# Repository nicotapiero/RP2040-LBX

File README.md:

# RP2040 LBX Compatible PCB

Initially forked from the [4.0 Version of the GRAM-SLIM](https://github.com/GRAMCTRL/GRAM-SLIM)

Thanks @beyondperfectly in the JFA Discord for the intial measurements: https://discord.com/channels/659775676542353438/888150700322861076/1038660816783802388

### Required Footprint Libraries:

* https://github.com/quark-works/qw-footprints/ (added as Git Submodule)
* [SW_choc_v1_HS_1u](https://github.com/ebastler/marbastlib/blob/6b0a9a73f579e377816d60b58eac2b3252de7868/footprints/marbastlib-choc.pretty/SW_choc_v1_HS_CPG135001S30_1u.kicad_mod)
* [SOIC-8_5.23x5.23mm_P1.27mm](https://github.com/KiCad/kicad-footprints/blob/master/Package_SO.pretty/SOIC-8_5.23x5.23mm_P1.27mm.kicad_mod)
* [CON_TC2030_outlined](https://github.com/ebastler/marbastlib/blob/6b0a9a73f579e377816d60b58eac2b3252de7868/footprints/marbastlib-various.pretty/CON_TC2030_outlined.kicad_mod)
* [ul_TS-1187A-B-A-B](https://app.ultralibrarian.com/details/34b5192a-fcd3-11ec-b159-0a34d6323d74/XKB-Connectivity/TS-1187A-B-A-B?open=backlink)

`.gitignore` for KiCad from [official Github repo](https://github.com/github/gitignore/blob/5b24c9042da72fcdcbe77dd5043243c987151d64/KiCad.gitignore)

Button layout to-scale diagram provided by LBX in their manual: https://docs.google.com/document/d/1tbTJEMjoW81OzD7IcGiDwz86cqZ35NQjBmwLq3tH4vI/edit?tab=t.0

Buttons confirmed rotated 9 degrees: https://discord.com/channels/659775676542353438/888150700322861076/1085662648756097205

PS Buttons confirmed TS-1187A-C-G-A or TS-1187A-C-G-B: https://discord.com/channels/659775676542353438/888150700322861076/1376599778439463015

## Disclaimer

This is an independent, community-developed replacement PCB compatible with the JFA LBX controller.

This project is not affiliated with, endorsed by, or sponsored by JFA. "JFA" and "LBX" are used solely to describe compatibility.

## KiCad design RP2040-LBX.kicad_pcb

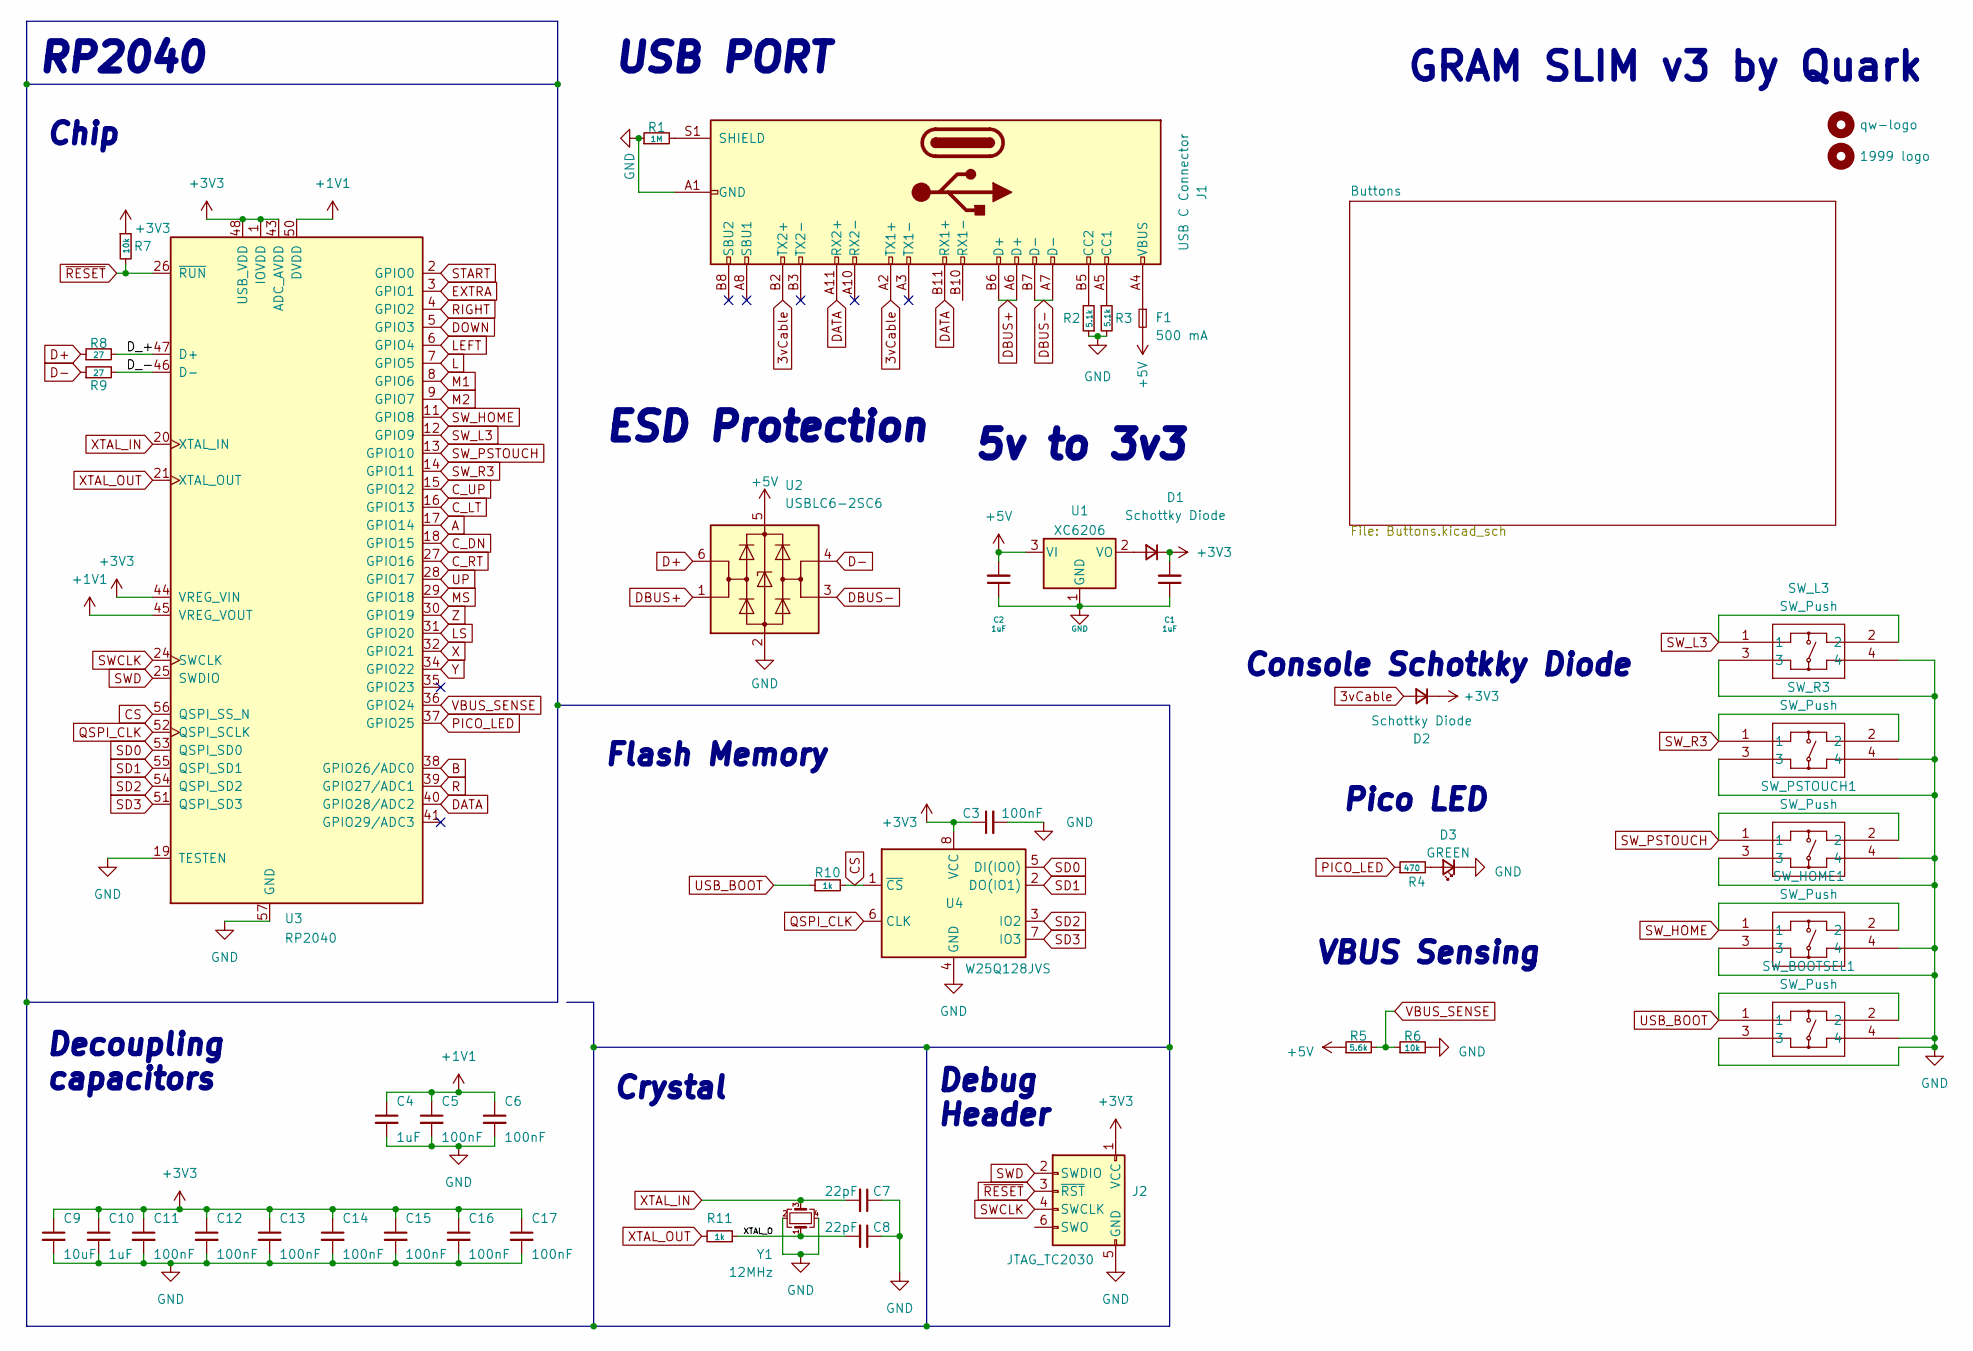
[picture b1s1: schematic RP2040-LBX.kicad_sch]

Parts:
C1, C2, C4, C10: 1uF; C_0402_1005Metric; LCSC C52923
C3, C5, C6, C11, C12, C13, C14, C15, C16, C17: 100nF; C_0402_1005Metric; LCSC C1525
C7, C8: 22pF; C_0402_1005Metric; LCSC C1555
C9: 10uF; C_0402_1005Metric; LCSC C15525
D1, D2: Schottky Diode; D_SOD-123; LCSC C130880
D3: GREEN; LED_0805_2012Metric; LCSC C2297
F1: 500 mA; Fuse_1206_3216Metric; LCSC C2836286
H1: qw-logo; qw new logo silk + copper md
H2: 1999 logo; 1999 logo md
J1: USB C Connector; TYPE-C_24P_QCHT; LCSC C456013
J2: JTAG_TC2030; CON_TC2030_outlined
R1: 1M; R_0603_1608Metric; LCSC C22935
R2, R3: 5.1k; R_0402_1005Metric; LCSC C25905
R4: 470; R_0402_1005Metric; LCSC C25117
R5: 5.6k; R_0603_1608Metric; LCSC C23189
R6: 10k; R_0603_1608Metric; LCSC C25804
R7: 10k; R_0402_1005Metric; LCSC C25744
R8, R9: 27; R_0603_1608Metric; LCSC C25190
R10, R11: 1k; R_0402_1005Metric; LCSC C11702
SW_BOOTSEL1: SW_Push; TS-1187A-B-A-B_XKB; LCSC C318886
SW_HOME1: SW_Push; TS-1187A-B-A-B_XKB; LCSC C318886
SW_L3: SW_Push; TS-1187A-B-A-B_XKB; LCSC C318886
SW_PSTOUCH1: SW_Push; TS-1187A-B-A-B_XKB; LCSC C318886
SW_R3: SW_Push; TS-1187A-B-A-B_XKB; LCSC C318886
U1: XC6206; SOT-23; LCSC C5446
U2: USBLC6-2SC6; SOT-23-6; LCSC C2827654
U3: RP2040; RP2040-QFN-56; LCSC C2040
U4: W25Q128JVS; SOIC-8_5.23x5.23mm_P1.27mm; LCSC C97521
Y1: 12MHz; Crystal_SMD_3225-4Pin_3.2x2.5mm; LCSC C9002

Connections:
3vCable: D2.2 (A), J1.A2 (TX1+), J1.B2 (TX2+)
+1V1: C4.1, C5.1, C6.1, U3.23 (DVDD), U3.45 (VREG_VOUT), U3.50 (DVDD)
+3V3: C1.2, C3.1, C9.1, C10.1, C11.1, C12.1, C13.1, C14.1, C15.1, C16.1, C17.1, D1.1 (K), D2.1 (K), J2.1 (VCC), R7.1, U3.1 (IOVDD), U3.10 (IOVDD), U3.22 (IOVDD), U3.33 (IOVDD), U3.42 (IOVDD), U3.43 (ADC_AVDD), U3.44 (VREG_VIN), U3.48 (USB_VDD), U3.49 (IOVDD), U4.8 (VCC)
+5V: C2.2, F1.2, R5.1, U1.3 (VI), U2.5 (VBUS)
/D_+: R8.2, U3.47 (D+)
/D_-: R9.2, U3.46 (D-)
/XTAL_O: C8.2, R11.1, Y1.1
A: U3.17 (GPIO14); also elsewhere on the board
B: U3.38 (GPIO26/ADC0); also elsewhere on the board
CS: R10.2, U3.56 (QSPI_SS_N), U4.1 (~CS)
C_DN: U3.18 (GPIO15); also elsewhere on the board
C_LT: U3.16 (GPIO13); also elsewhere on the board
C_RT: U3.27 (GPIO16); also elsewhere on the board
C_UP: U3.15 (GPIO12); also elsewhere on the board
D+: R8.1, U2.6 (I/O1)
D-: R9.1, U2.4 (I/O2)
DATA: J1.A11 (RX2+), J1.B11 (RX1+), U3.40 (GPIO28/ADC2)
DBUS+: J1.A6 (D+), J1.B6 (D+), U2.1 (I/O1)
DBUS-: J1.A7 (D-), J1.B7 (D-), U2.3 (I/O2)
DOWN: U3.5 (GPIO3); also elsewhere on the board
EXTRA: U3.3 (GPIO1); also elsewhere on the board
GND: C1.1, C2.1, C3.2, C4.2, C5.2, C6.2, C7.1, C8.1, C9.2, C10.2, C11.2, C12.2, C13.2, C14.2, C15.2, C16.2, C17.2, D3.1 (K), J1.A1 (GND), J1.A12 (GND), J1.B1 (GND), J1.B12 (GND), J2.5 (GND), R1.1, R2.1, R3.2, R6.2, SW_BOOTSEL1.3, SW_BOOTSEL1.4, SW_HOME1.3, SW_HOME1.4, SW_L3.3, SW_L3.4, SW_PSTOUCH1.3, SW_PSTOUCH1.4, SW_R3.3, SW_R3.4, U1.1 (GND), U2.2 (GND), U3.19 (TESTEN), U3.57 (GND), U4.4 (GND), Y1.2, Y1.4; also elsewhere on the board
L: U3.7 (GPIO5); also elsewhere on the board
LEFT: U3.6 (GPIO4); also elsewhere on the board
LS: U3.31 (GPIO20); also elsewhere on the board
M1: U3.8 (GPIO6); also elsewhere on the board
M2: U3.9 (GPIO7); also elsewhere on the board
MS: U3.29 (GPIO18); also elsewhere on the board
unnamed: D1.2 (A), U1.2 (VO)
unnamed: D3.2 (A), R4.2
unnamed: F1.1, J1.A4 (VBUS), J1.A9 (VBUS), J1.B4 (VBUS), J1.B9 (VBUS)
unnamed: J1.A5 (CC1), R3.1
unnamed: J1.B5 (CC2), R2.2
unnamed: J1.S1 (SHIELD), R1.2
PICO_LED: R4.1, U3.37 (GPIO25)
QSPI_CLK: U3.52 (QSPI_SCLK), U4.6 (CLK)
R: U3.39 (GPIO27/ADC1); also elsewhere on the board
RIGHT: U3.4 (GPIO2); also elsewhere on the board
SD0: U3.53 (QSPI_SD0), U4.5 (DI(IO0))
SD1: U3.55 (QSPI_SD1), U4.2 (DO(IO1))
SD2: U3.54 (QSPI_SD2), U4.3 (IO2)
SD3: U3.51 (QSPI_SD3), U4.7 (IO3)
START: U3.2 (GPIO0); also elsewhere on the board
SWCLK: J2.4 (SWCLK), U3.24 (SWCLK)
SWD: J2.2 (SWDIO), U3.25 (SWDIO)
SW_HOME: SW_HOME1.1, SW_HOME1.2, U3.11 (GPIO8)
SW_L3: SW_L3.1, SW_L3.2, U3.12 (GPIO9)
SW_PSTOUCH: SW_PSTOUCH1.1, SW_PSTOUCH1.2, U3.13 (GPIO10)
SW_R3: SW_R3.1, SW_R3.2, U3.14 (GPIO11)
UP: U3.28 (GPIO17); also elsewhere on the board
USB_BOOT: R10.1, SW_BOOTSEL1.1, SW_BOOTSEL1.2
VBUS_SENSE: R5.2, R6.1, U3.36 (GPIO24)
X: U3.32 (GPIO21); also elsewhere on the board
XTAL_IN: C7.2, U3.20 (XTAL_IN), Y1.3
XTAL_OUT: R11.2, U3.21 (XTAL_OUT)
Y: U3.34 (GPIO22); also elsewhere on the board
Z: U3.30 (GPIO19); also elsewhere on the board
~RESET: J2.3 (~RST), R7.2, U3.26 (~RUN)

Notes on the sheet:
GRAM SLIM v3 by Quark
Flash Memory
5v to 3v3
Pico LED
Crystal
Chip
Console Schotkky Diode
RP2040
VBUS Sensing
Debug Header
USB PORT
ESD Protection
Decoupling capacitors

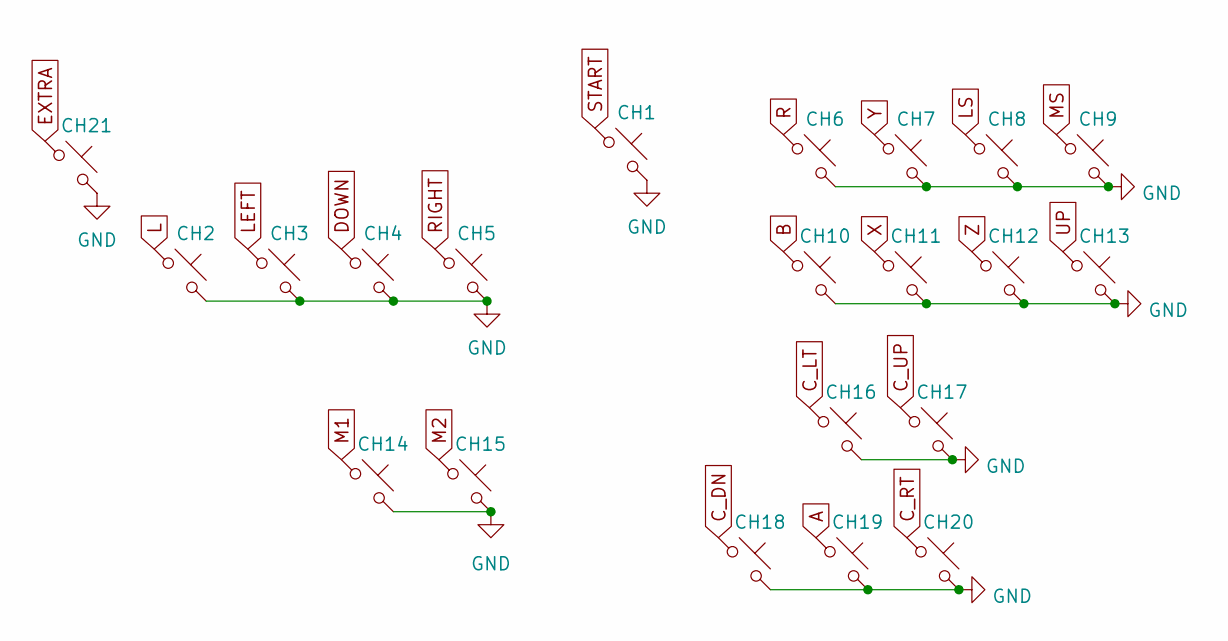
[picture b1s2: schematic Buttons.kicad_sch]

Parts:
CH1, CH2, CH3, CH4, CH5, CH6, CH7, CH8, CH9, CH10, CH11, CH12, CH13, CH14, CH15, CH16, CH17, CH18, CH19, CH20, CH21: choc_SW_HS; SW_choc_v1_HS_1u

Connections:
A: CH19.1; also elsewhere on the board
B: CH10.1; also elsewhere on the board
C_DN: CH18.1; also elsewhere on the board
C_LT: CH16.1; also elsewhere on the board
C_RT: CH20.1; also elsewhere on the board
C_UP: CH17.1; also elsewhere on the board
DOWN: CH4.1; also elsewhere on the board
EXTRA: CH21.1; also elsewhere on the board
GND: CH1.2, CH2.2, CH3.2, CH4.2, CH5.2, CH6.2, CH7.2, CH8.2, CH9.2, CH10.2, CH11.2, CH12.2, CH13.2, CH14.2, CH15.2, CH16.2, CH17.2, CH18.2, CH19.2, CH20.2, CH21.2; also elsewhere on the board
L: CH2.1; also elsewhere on the board
LEFT: CH3.1; also elsewhere on the board
LS: CH8.1; also elsewhere on the board
M1: CH14.1; also elsewhere on the board
M2: CH15.1; also elsewhere on the board
MS: CH9.1; also elsewhere on the board
R: CH6.1; also elsewhere on the board
RIGHT: CH5.1; also elsewhere on the board
START: CH1.1; also elsewhere on the board
UP: CH13.1; also elsewhere on the board
X: CH11.1; also elsewhere on the board
Y: CH7.1; also elsewhere on the board
Z: CH12.1; also elsewhere on the board

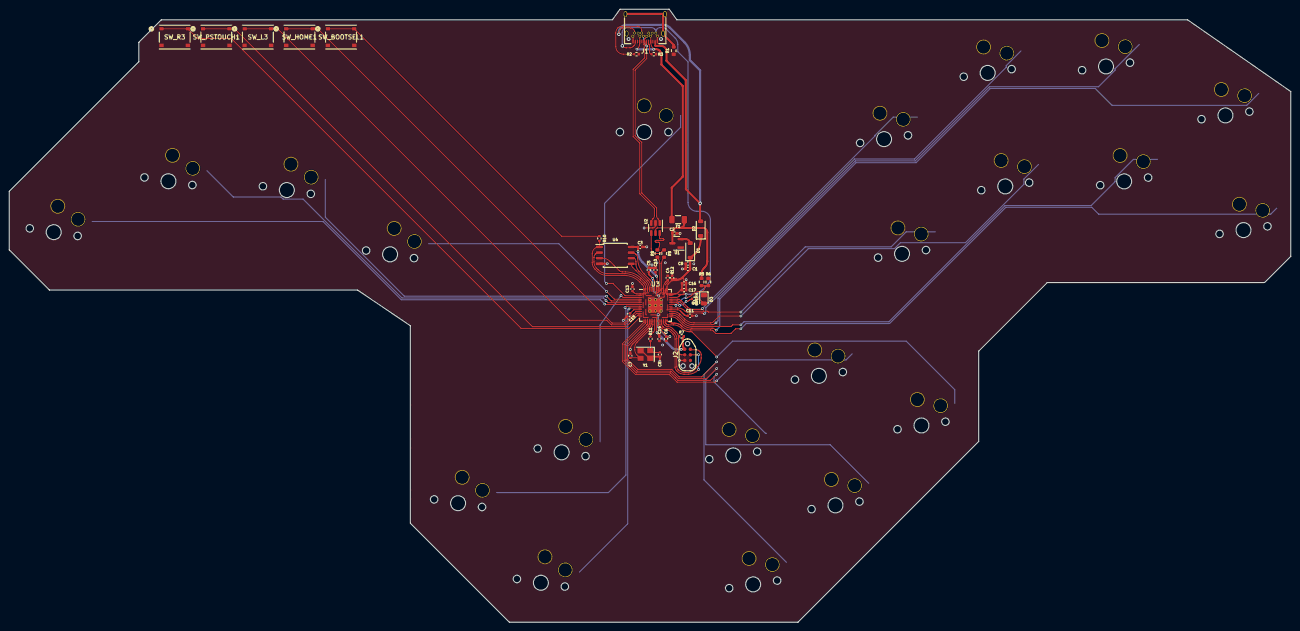
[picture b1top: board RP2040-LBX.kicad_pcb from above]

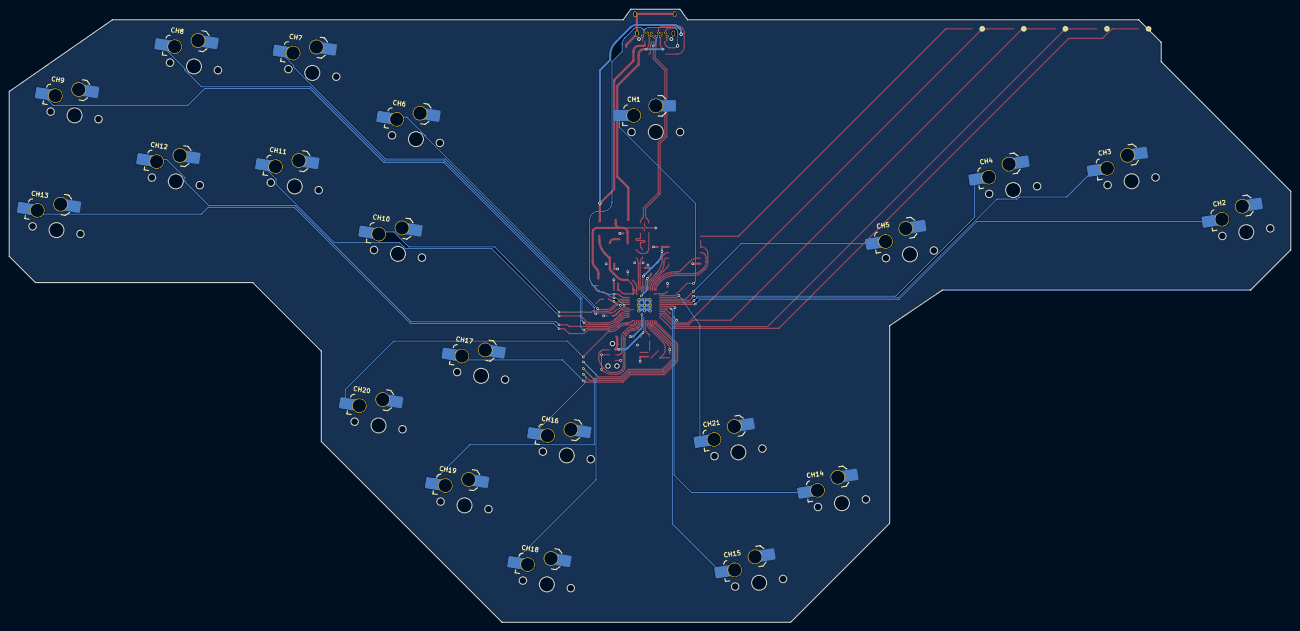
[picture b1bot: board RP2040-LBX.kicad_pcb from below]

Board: 2 copper layers, 290.7 x 139.1 mm, 65 parts (21 on the bottom side), 58 nets.
